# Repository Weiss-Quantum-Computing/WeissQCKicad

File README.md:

# WeissQCKicad
Kicad files for David S Weiss's Quantum Computing Experiment

Kicad files generally include a project file, schematic, and PCB file. Finished projects that have been sent to fabrication will also contain a set of gerber files defining the layers for fabrication. Projects exist in various states of completion and functionality so double check your work.

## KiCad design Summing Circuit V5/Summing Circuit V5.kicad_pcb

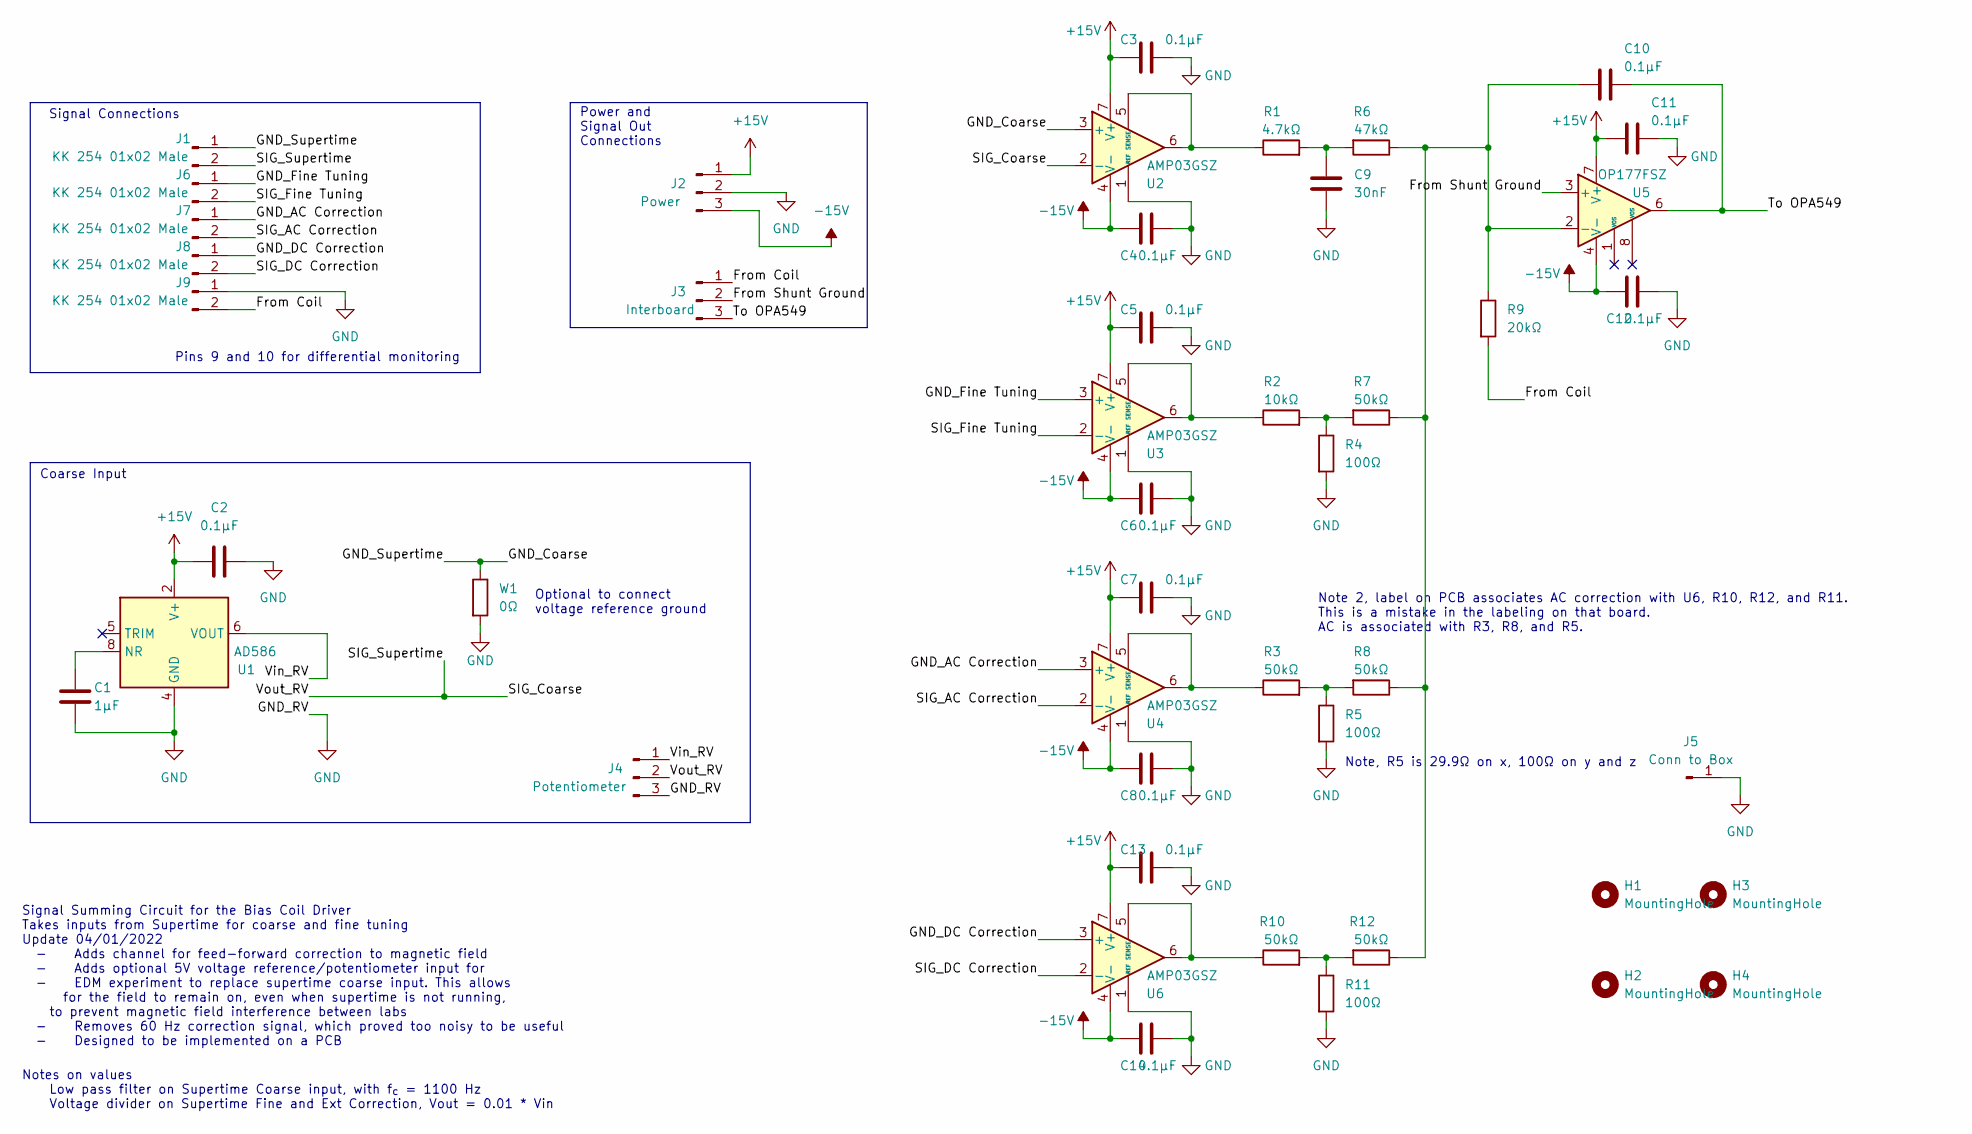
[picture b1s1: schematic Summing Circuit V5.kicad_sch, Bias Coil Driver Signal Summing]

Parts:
C1: 1µF; C_1206_3216Metric
C2, C3, C4, C5, C6, C7, C8, C10, C11, C12, C13, C14: 0.1µF; C_1206_3216Metric
C9: 30nF; C_1206_3216Metric
H1, H2, H3, H4: MountingHole; MountingHole_4.3mm_M4
J1, J6, J7, J8, J9: KK 254 01x02 Male; Molex_KK-254_AE-6410-02A_1x02_P2.54mm_Vertical
J2: Power; Molex_KK-254_AE-6410-03A_1x03_P2.54mm_Vertical
J3: Interboard; Molex_KK-254_AE-6410-03A_1x03_P2.54mm_Vertical
J4: Potentiometer; Molex_KK-254_AE-6410-03A_1x03_P2.54mm_Vertical
J5: Conn to Box; TestPoint_Pad_2.0x2.0mm
R1: 4.7kΩ; R_1206_3216Metric
R2: 10kΩ; R_1206_3216Metric
R3, R7, R8, R10, R12: 50kΩ; R_1206_3216Metric
R4, R5, R11: 100Ω; R_1206_3216Metric
R6: 47kΩ; R_1206_3216Metric
R9: 20kΩ; R_1206_3216Metric
U1: AD586; SOIC-8_3.9x4.9mm_P1.27mm
U2, U3, U4, U6: AMP03GSZ; SOIC-8_3.9x4.9mm_P1.27mm
U5: OP177FSZ; SOIC-8_3.9x4.9mm_P1.27mm
W1: 0Ω; R_1206_3216Metric

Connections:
+15V: C2.1, C3.2, C5.2, C7.2, C11.2, C13.2, J2.1, U1.2 (V+), U2.7 (V+), U3.7 (V+), U4.7 (V+), U5.7 (V+), U6.7 (V+)
-15V: C4.2, C6.2, C8.2, C12.2, C14.2, J2.3, U2.4 (V-), U3.4 (V-), U4.4 (V-), U5.4 (V-), U6.4 (V-)
/From Coil: J3.1, J9.2, R9.2
/From Shunt Ground: J3.2, U5.3 (+)
/GND_AC Correction: J7.1, U4.3 (+)
/GND_Coarse: J1.1, U2.3 (+), W1.1
/GND_DC Correction: J8.1, U6.3 (+)
/GND_Fine Tuning: J6.1, U3.3 (+)
/SIG_AC Correction: J7.2, U4.2 (-)
/SIG_Coarse: J1.2, J4.2, U2.2 (-)
/SIG_DC Correction: J8.2, U6.2 (-)
/SIG_Fine Tuning: J6.2, U3.2 (-)
/To OPA549: C10.1, J3.3, U5.6
/Vin_RV: J4.1, U1.6 (VOUT)
GND: C1.2, C2.2, C3.1, C4.1, C5.1, C6.1, C7.1, C8.1, C9.2, C11.1, C12.1, C13.1, C14.1, J2.2, J4.3, J5.1, J9.1, R4.2, R5.2, R11.2, U1.4 (GND), U2.1 (REF), U3.1 (REF), U4.1 (REF), U6.1 (REF), W1.2
unnamed: C1.1, U1.8 (NR)
unnamed: C9.1, R1.2, R6.2
unnamed: C10.2, R6.1, R7.1, R8.1, R9.1, R12.1, U5.2 (-)
unnamed: R1.1, U2.5 (SENSE), U2.6
unnamed: R2.1, U3.5 (SENSE), U3.6
unnamed: R2.2, R4.1, R7.2
unnamed: R3.1, U4.5 (SENSE), U4.6
unnamed: R3.2, R5.1, R8.2
unnamed: R10.1, U6.5 (SENSE), U6.6
unnamed: R10.2, R11.1, R12.2

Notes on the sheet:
Optional to connect voltage reference ground
Power and Signal Out Connections
Note, R5 is 29.9Ω on x, 100Ω on y and z
Pins 9 and 10 for differential monitoring
Notes on values Low pass filter on Supertime Coarse input, with f_{c} = 1100 Hz Voltage divider on Supertime Fine and Ext Correction, Vout = 0.01 * Vin
Coarse Input
Note 2, label on PCB associates AC correction with U6, R10, R12, and R11. This is a mistake in the labeling on that board. AC is associated with R3, R8, and R5.
Signal Connections
Signal Summing Circuit for the Bias Coil Driver Takes inputs from Supertime for coarse and fine tuning Update 04/01/2022 - Adds channel for feed-forward correction to magnetic field - Adds optional 5V voltage reference/potentiometer input for - EDM experiment to replace supertime coarse input. This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

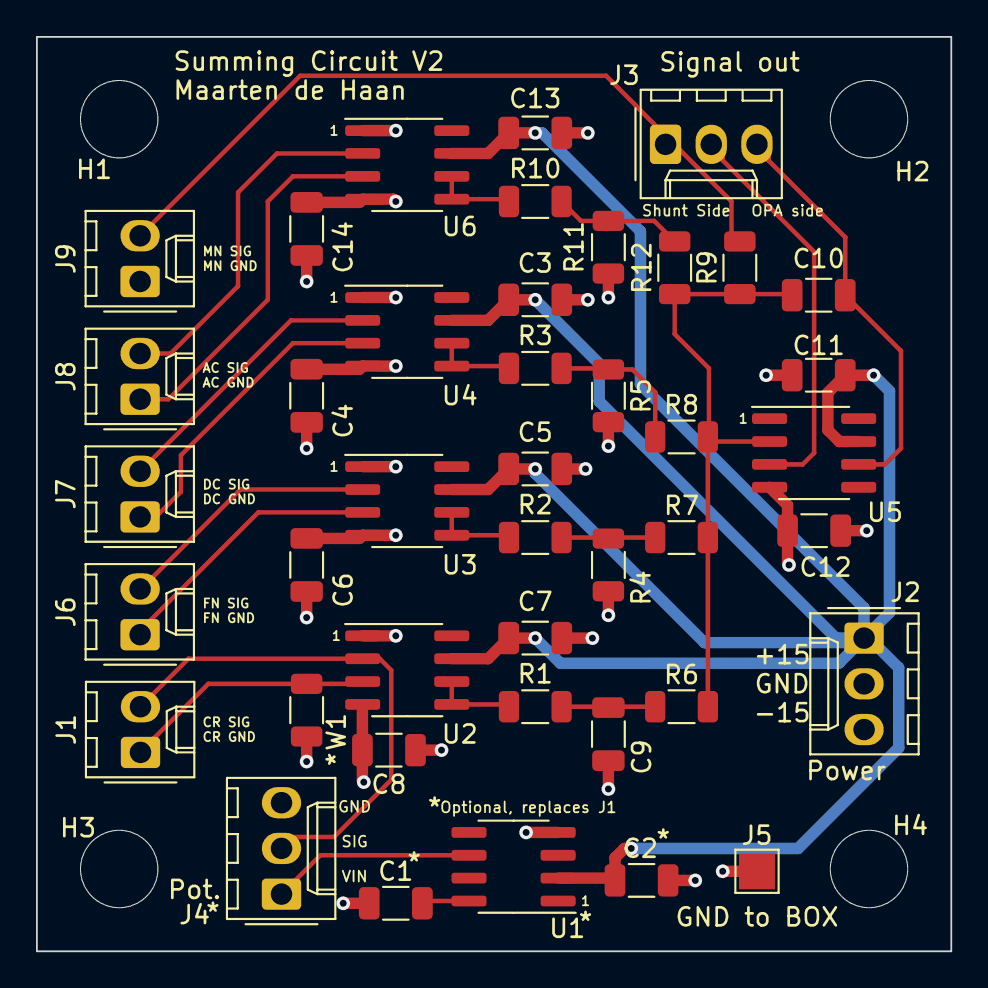
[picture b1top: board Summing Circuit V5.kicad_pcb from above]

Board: 4 copper layers, 50.8 x 50.8 mm, 46 parts (0 on the bottom side), 25 nets.

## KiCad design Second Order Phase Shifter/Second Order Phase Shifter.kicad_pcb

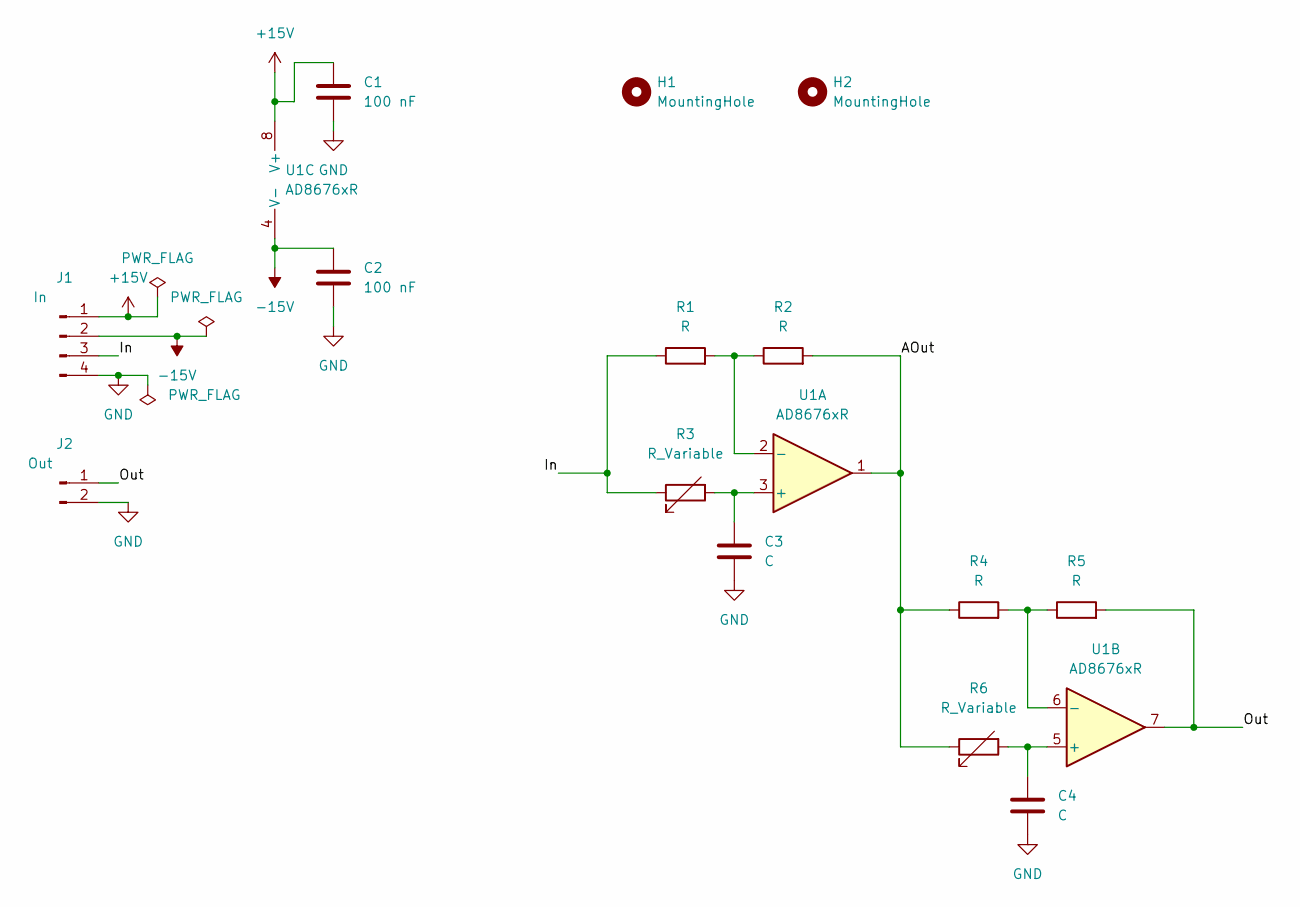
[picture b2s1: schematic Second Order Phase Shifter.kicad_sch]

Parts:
C1, C2: 100 nF; C_1206_3216Metric
C3, C4: C; C_1206_3216Metric
H1, H2: MountingHole; MountingHole_3.2mm_M3
J1: In; Molex_KK-254_AE-6410-04A_1x04_P2.54mm_Vertical
J2: Out; Molex_KK-254_AE-6410-02A_1x02_P2.54mm_Vertical
R1, R2, R4, R5: R; R_1206_3216Metric
R3, R6: R_Variable; Molex_KK-254_AE-6410-02A_1x02_P2.54mm_Vertical
U1: AD8676xR; SOIC-8_3.9x4.9mm_P1.27mm

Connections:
+15V: C1.1, J1.1, U1.8 (V+)
-15V: C2.1, J1.2, U1.4 (V-)
/AOut: R2.2, R4.1, R6.1, U1.1
/In: J1.3, R1.1, R3.1
/Out: J2.1, R5.2, U1.7
GND: C1.2, C2.2, C3.1, C4.1, J1.4, J2.2
unnamed: R1.2, R2.1, U1.2 (-)
unnamed: C3.2, R3.2, U1.3 (+)
unnamed: R4.2, R5.1, U1.6 (-)
unnamed: C4.2, R6.2, U1.5 (+)

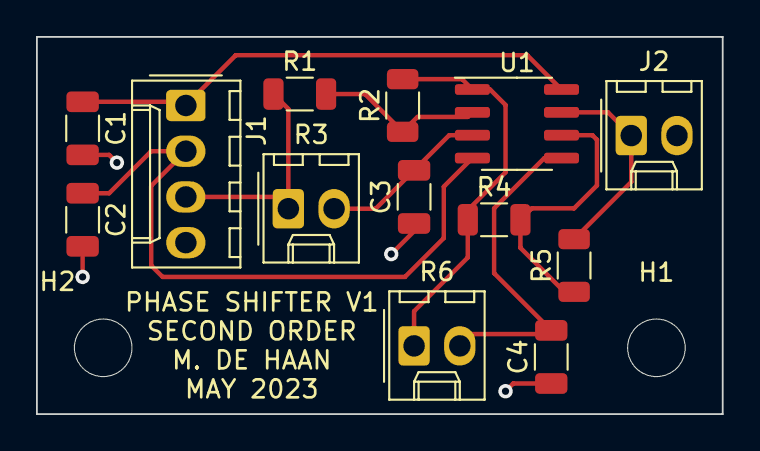
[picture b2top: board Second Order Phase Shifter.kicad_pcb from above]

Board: 2 copper layers, 38.1 x 21.0 mm, 15 parts (0 on the bottom side), 10 nets.

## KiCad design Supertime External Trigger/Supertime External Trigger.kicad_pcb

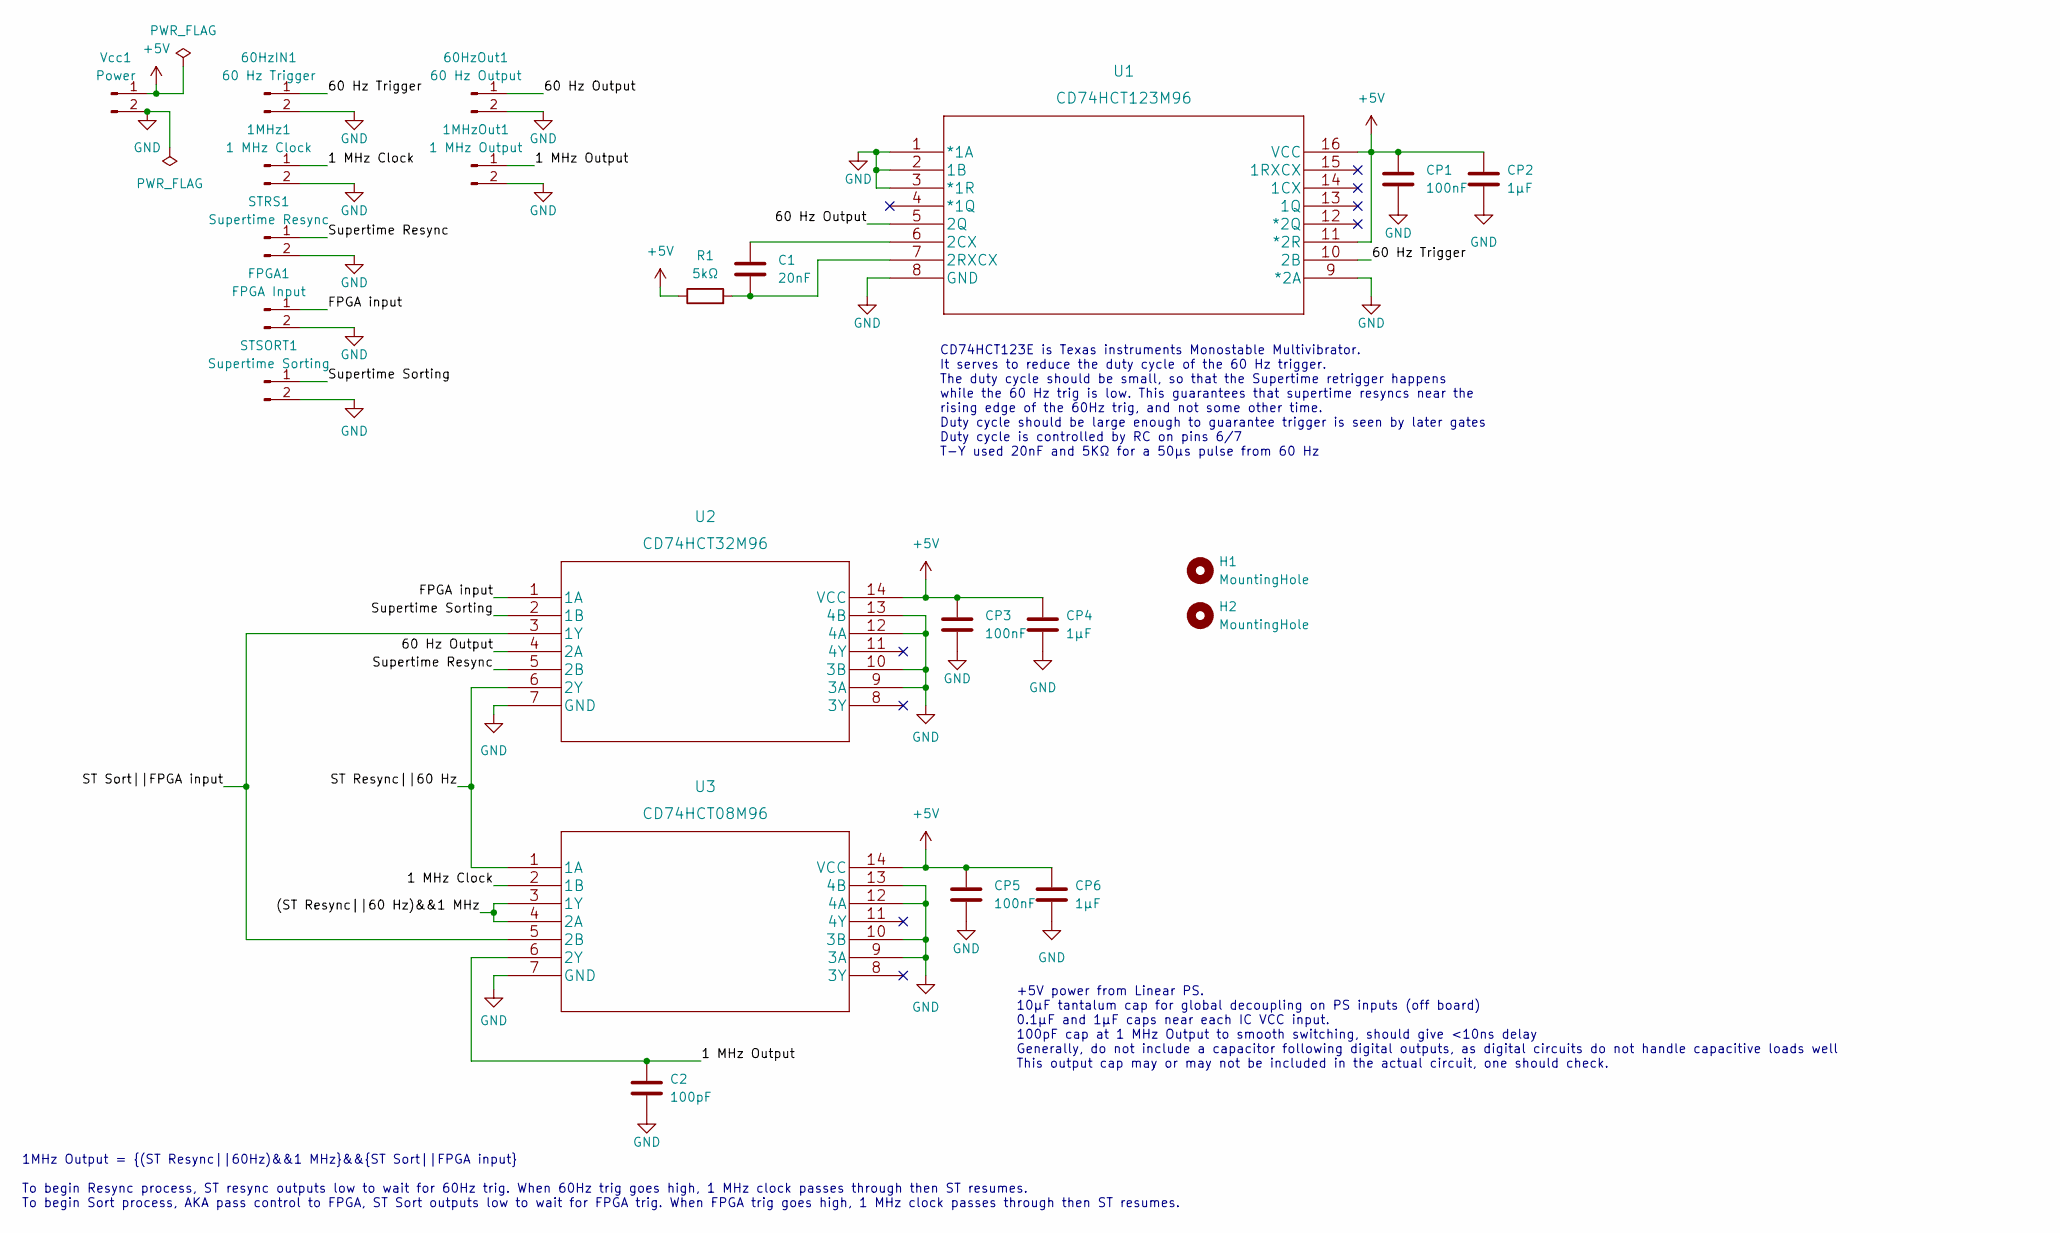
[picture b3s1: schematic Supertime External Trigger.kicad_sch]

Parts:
1MHz1: 1 MHz Clock; Molex_KK-254_AE-6410-02A_1x02_P2.54mm_Vertical
1MHzOut1: 1 MHz Output; Molex_KK-254_AE-6410-02A_1x02_P2.54mm_Vertical
60HzIN1: 60 Hz Trigger; Molex_KK-254_AE-6410-02A_1x02_P2.54mm_Vertical
60HzOut1: 60 Hz Output; Molex_KK-254_AE-6410-02A_1x02_P2.54mm_Vertical
C1: 20nF; C_1206_3216Metric
C2: 100pF; C_1206_3216Metric
CP1, CP3, CP5: 100nF; C_1206_3216Metric
CP2, CP4, CP6: 1µF; C_1206_3216Metric
FPGA1: FPGA Input; Molex_KK-254_AE-6410-02A_1x02_P2.54mm_Vertical
H1, H2: MountingHole; MountingHole_3.2mm_M3
R1: 5kΩ; R_1206_3216Metric
STRS1: Supertime Resync; Molex_KK-254_AE-6410-02A_1x02_P2.54mm_Vertical
STSORT1: Supertime Sorting; Molex_KK-254_AE-6410-02A_1x02_P2.54mm_Vertical
U1: CD74HCT123M96; SOIC-16_3.9x9.9mm_P1.27mm
U2: CD74HCT32M96; SOIC-14_3.9x8.7mm_P1.27mm
U3: CD74HCT08M96; SOIC-14_3.9x8.7mm_P1.27mm
Vcc1: Power; Molex_KK-254_AE-6410-02A_1x02_P2.54mm_Vertical

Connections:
+5V: CP1.1, CP2.1, CP3.1, CP4.1, CP5.1, CP6.1, R1.1, U1.11 (*2R), U1.16 (VCC), U2.14 (VCC), U3.14 (VCC), Vcc1.1
/1 MHz Clock: 1MHz1.1, U3.2 (1B)
/1 MHz Output: 1MHzOut1.1, C2.1, U3.6 (2Y)
/60 Hz Output: 60HzOut1.1, U1.5 (2Q), U2.4 (2A)
/60 Hz Trigger: 60HzIN1.1, U1.10 (2B)
/(ST Resync||60 Hz)&&1 MHz: U3.3 (1Y), U3.4 (2A)
/FPGA input: FPGA1.1, U2.1 (1A)
/ST Resync||60 Hz: U2.6 (2Y), U3.1 (1A)
/ST Sort||FPGA input: U2.3 (1Y), U3.5 (2B)
/Supertime Resync: STRS1.1, U2.5 (2B)
/Supertime Sorting: STSORT1.1, U2.2 (1B)
GND: 1MHz1.2, 1MHzOut1.2, 60HzIN1.2, 60HzOut1.2, C2.2, CP1.2, CP2.2, CP3.2, CP4.2, CP5.2, CP6.2, FPGA1.2, STRS1.2, STSORT1.2, U1.1 (*1A), U1.2 (1B), U1.3 (*1R), U1.8 (GND), U1.9 (*2A), U2.7 (GND), U2.9 (3A), U2.10 (3B), U2.12 (4A), U2.13 (4B), U3.7 (GND), U3.9 (3A), U3.10 (3B), U3.12 (4A), U3.13 (4B), Vcc1.2
unnamed: C1.1, U1.6 (2CX)
unnamed: C1.2, R1.2, U1.7 (2RXCX)

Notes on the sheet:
+5V power from Linear PS. 10µF tantalum cap for global decoupling on PS inputs (off board) 0.1µF and 1µF caps near each IC VCC input. 100pF cap at 1 MHz Output to smooth switching, should give <10ns delay Generally, do not include a capacitor following digital outputs, as digital circuits do not ha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
1MHz Output = {(ST Resync||60Hz)&&1 MHz}&&{ST Sort||FPGA input} To begin Resync process, ST resync outputs low to wait for 60Hz trig. When 60Hz trig goes high, 1 MHz clock passes through then ST resumes. To begin Sort process, AKA pass control to FPGA, ST Sort outputs low to wait for FPGA trig. Whe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
CD74HCT123E is Texas instruments Monostable Multivibrator. It serves to reduce the duty cycle of the 60 Hz trigger. The duty cycle should be small, so that the Supertime retrigger happens while the 60 Hz trig is low. This guarantees that supertime resyncs near the rising edge of the 60Hz trig, and 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

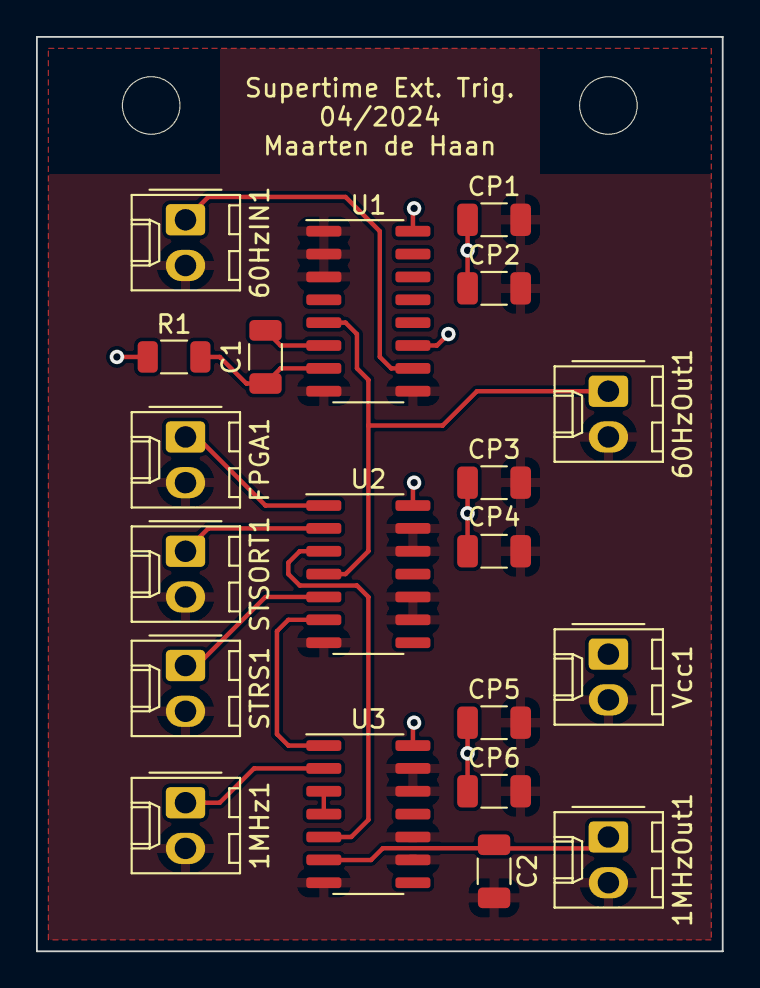
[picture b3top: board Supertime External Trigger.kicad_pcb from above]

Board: 2 copper layers, 38.1 x 50.8 mm, 22 parts (0 on the bottom side), 14 nets.

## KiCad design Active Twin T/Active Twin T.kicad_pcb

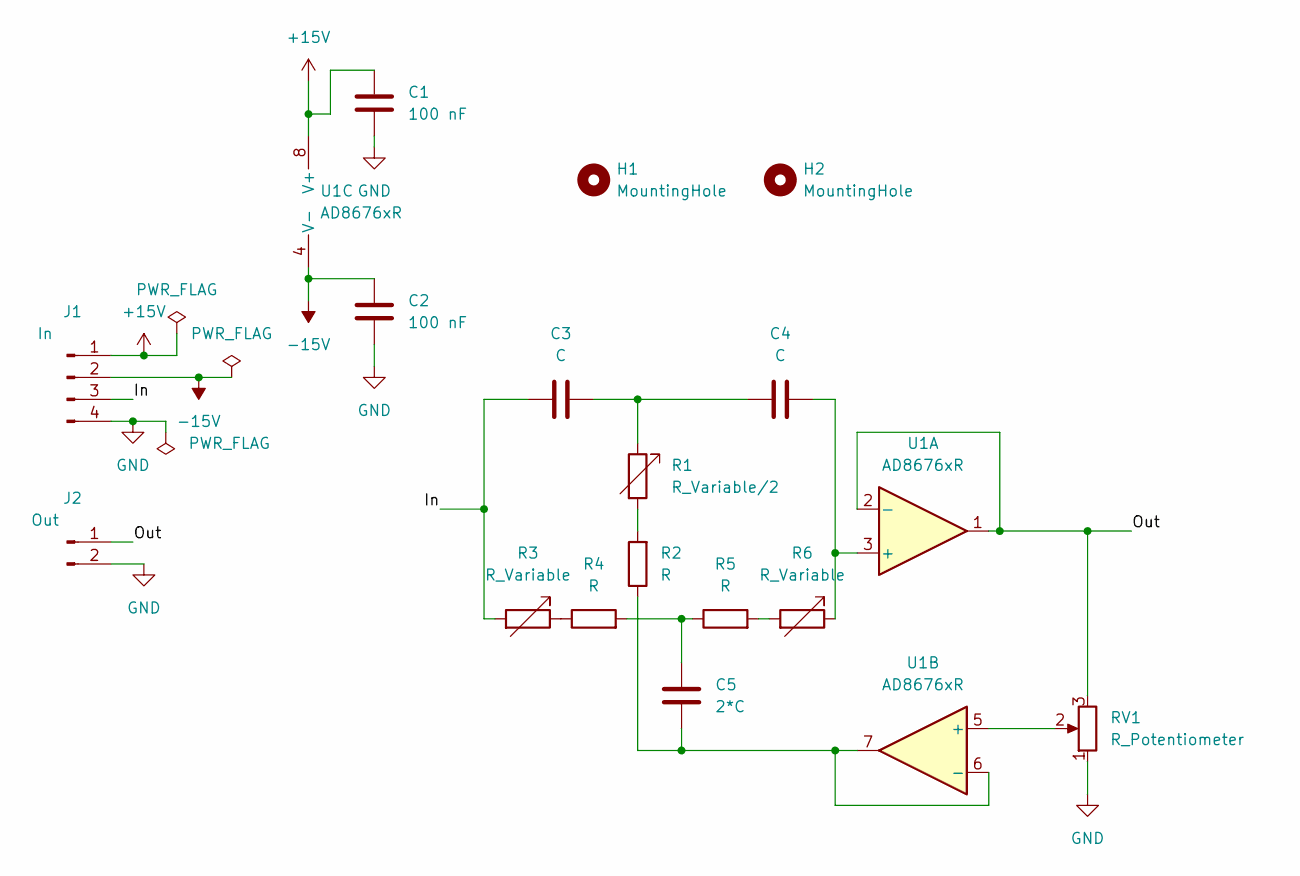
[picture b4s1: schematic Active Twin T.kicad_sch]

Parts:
C1, C2: 100 nF; C_1206_3216Metric
C3, C4: C; C_1206_3216Metric
C5: 2*C; C_1206_3216Metric
H1, H2: MountingHole; MountingHole_3.2mm_M3
J1: In; Molex_KK-254_AE-6410-04A_1x04_P2.54mm_Vertical
J2: Out; Molex_KK-254_AE-6410-02A_1x02_P2.54mm_Vertical
R1: R_Variable/2; Molex_KK-254_AE-6410-02A_1x02_P2.54mm_Vertical
R2, R4, R5: R; R_1206_3216Metric
R3, R6: R_Variable; Molex_KK-254_AE-6410-02A_1x02_P2.54mm_Vertical
RV1: R_Potentiometer; Molex_KK-254_AE-6410-03A_1x03_P2.54mm_Vertical
U1: AD8676xR; SOIC-8_3.9x4.9mm_P1.27mm

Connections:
+15V: C1.1, J1.1, U1.8 (V+)
-15V: C2.1, J1.2, U1.4 (V-)
/In: C3.1, J1.3, R3.2
/Out: J2.1, RV1.3, U1.1, U1.2 (-)
GND: C1.2, C2.2, J1.4, J2.2, RV1.1
unnamed: C3.2, C4.1, R1.1
unnamed: C4.2, R6.1, U1.3 (+)
unnamed: C5.1, R2.1, U1.6 (-), U1.7
unnamed: C5.2, R4.2, R5.1
unnamed: R1.2, R2.2
unnamed: R3.1, R4.1
unnamed: R5.2, R6.2
unnamed: RV1.2, U1.5 (+)

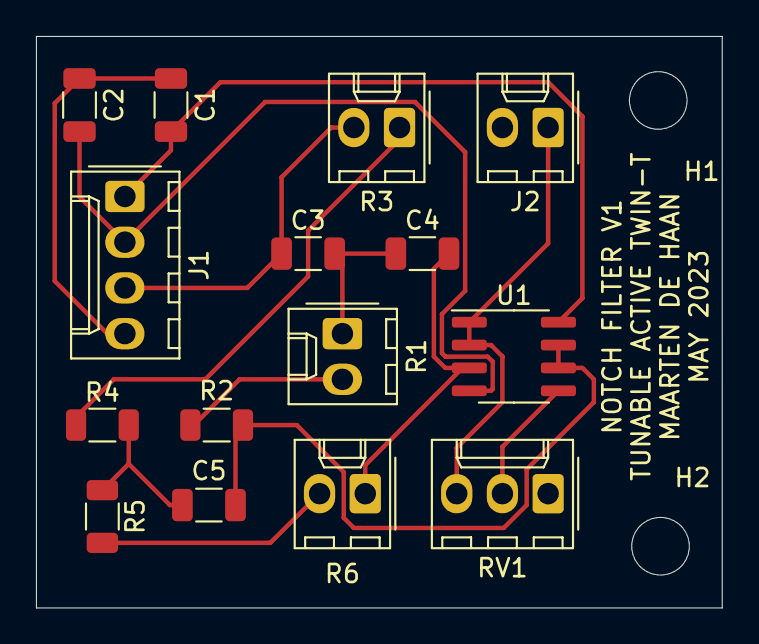
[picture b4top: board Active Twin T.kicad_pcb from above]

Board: 2 copper layers, 38.1 x 31.7 mm, 17 parts (0 on the bottom side), 13 nets.

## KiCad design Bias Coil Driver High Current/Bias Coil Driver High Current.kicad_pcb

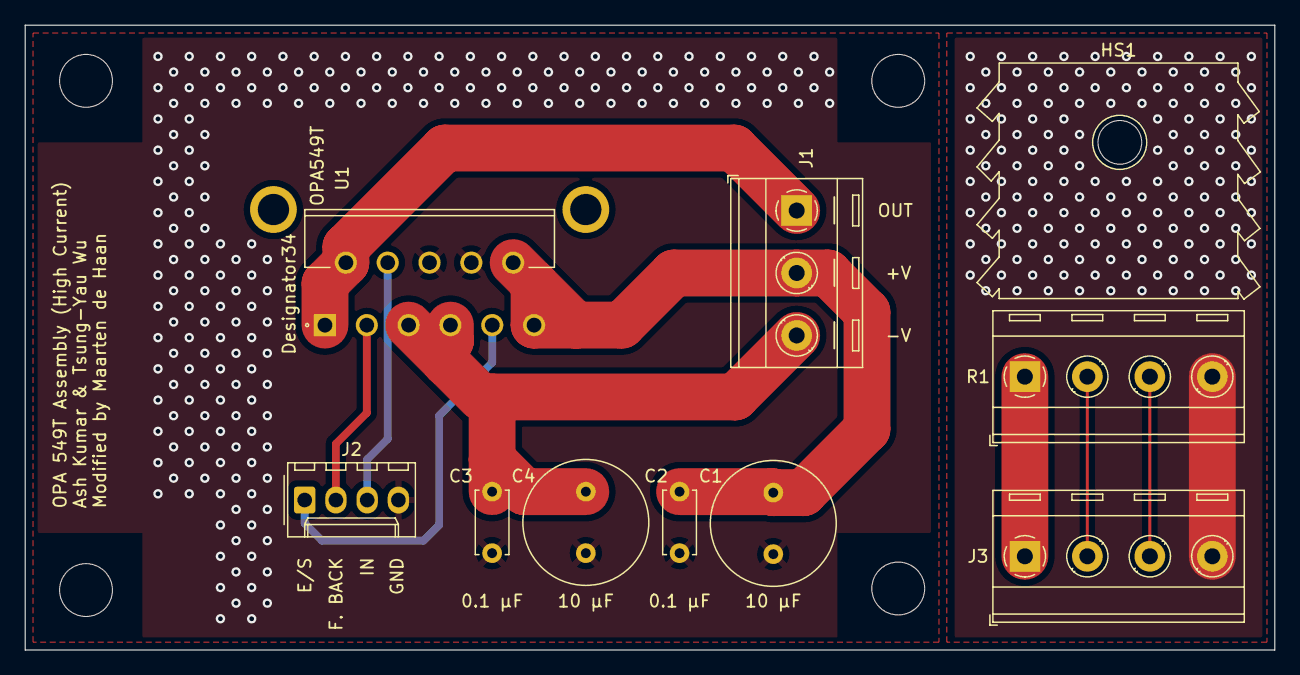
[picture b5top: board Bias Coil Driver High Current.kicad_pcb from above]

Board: 2 copper layers, 101.6 x 50.8 mm, 14 parts (0 on the bottom side), 11 nets.

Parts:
C1, C4: 10 µF; C_Radial_D10.0mm_H16.0mm_P5.00mm
C2, C3: 0.1 µF; C_Disc_D5.0mm_W2.5mm_P5.00mm
H1, H2, H3, H4: MountingHole; MountingHole_4.3mm_M4
HS1: Heatsink; Heatsink_Aavid-TV5G_TO220_Horizontal
J1: 1x03 Terminal Block; TerminalBlock_RND_205-00288_1x03_P5.08mm_Horizontal
J2: KK 254 1x04 Male; Molex_KK-254_AE-6410-04A_1x04_P2.54mm_Vertical
J3: 4 pin Terminal Block; TerminalBlock_RND_205-00289_1x04_P5.08mm_Horizontal
R1: R_Shunt; TerminalBlock_RND_205-00289_1x04_P5.08mm_Horizontal
U1: OPA549T

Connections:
+VDC: C1.2, C2.2, J1.2, U1.10 (V+), U1.11 (V+)
-VDC: C3.2, C4.2, J1.3, U1.5 (V-), U1.7 (V-)
/E/S: J2.1, U1.9 (E/S)
/Feedback: J2.2, U1.3 (-IN)
/In: J2.3, U1.4 (+IN)
/Out: J1.1, U1.1, U1.2
GND: C1.1, C2.1, C3.1, C4.1, J2.4, U1.6 (Ref), U1.8 (ILIM)
GND2: J3.4, R1.4
unnamed: J3.1, R1.1
unnamed: J3.2, R1.2
unnamed: J3.3, R1.3

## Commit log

2024-06-17 Update README.md
    added description

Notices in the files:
parts and their libraries:
Copyright 2021 Accelerated Designs. All rights reserved.
